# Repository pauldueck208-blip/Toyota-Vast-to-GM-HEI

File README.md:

# Toyota-Vast-to-GM-HEI
Board and code that interfaces between a GM HEI 8 pin and a 22re to replace the factory igniter.

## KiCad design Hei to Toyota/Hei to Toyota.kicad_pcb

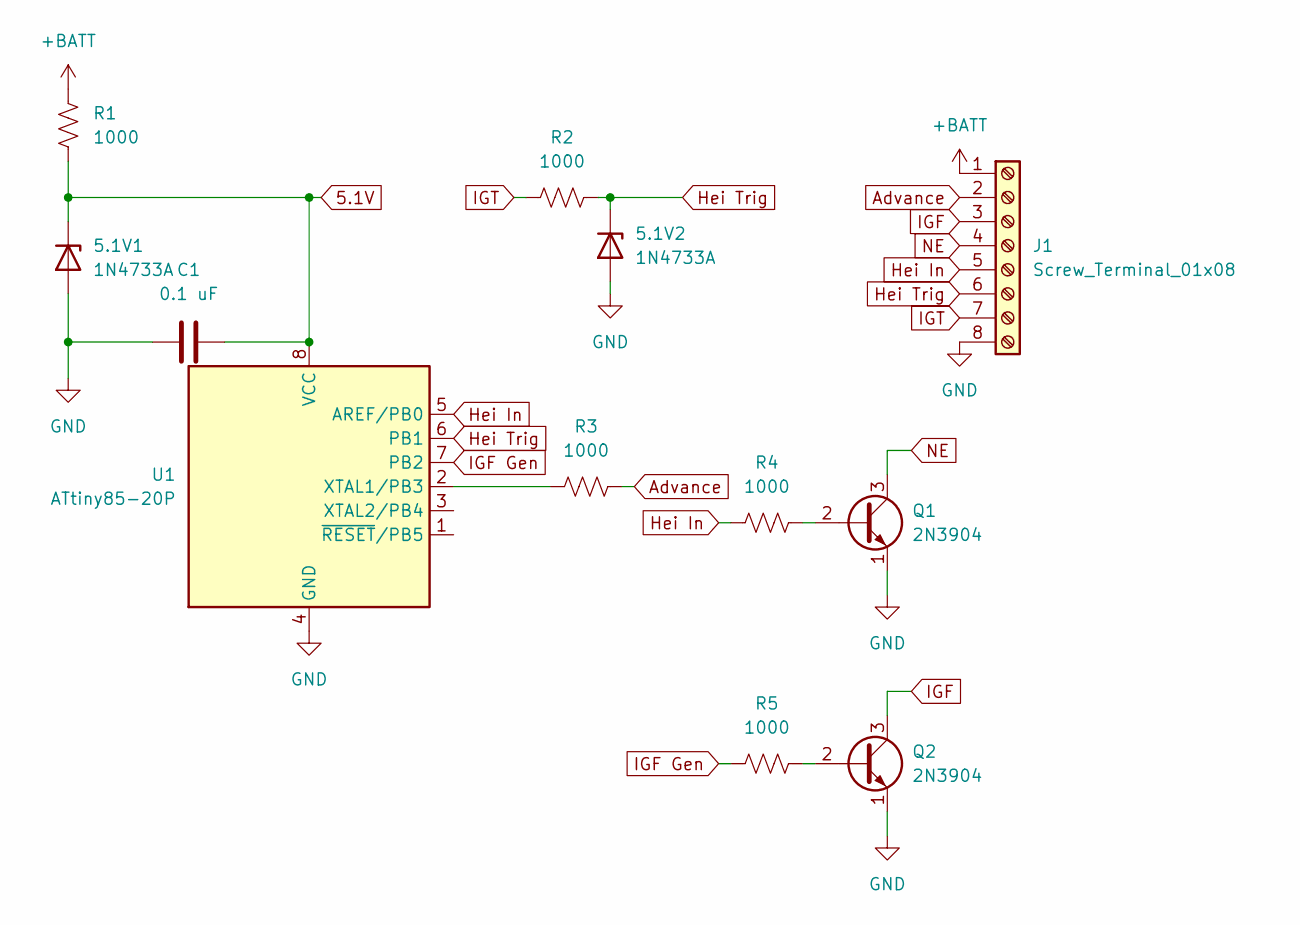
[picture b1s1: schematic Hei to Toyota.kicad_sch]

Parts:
5.1V1, 5.1V2: 1N4733A; D_DO-41_SOD81_P10.16mm_Horizontal
C1: 0.1 uF; C_Disc_D5.0mm_W2.5mm_P2.50mm
J1: Screw_Terminal_01x08; TerminalBlock_MaiXu_MX126-5.0-08P_1x08_P5.00mm
Q1, Q2: 2N3904; TO-92_Inline
R1, R2, R3, R4, R5: 1000; R_Axial_DIN0207_L6.3mm_D2.5mm_P10.16mm_Horizontal
U1: ATtiny85-20P; DIP-8_W7.62mm

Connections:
5.1V: 5.1V1.1 (K), C1.1, R1.1, U1.8 (VCC)
+BATT: J1.1, R1.2
Advance: J1.2, R3.2
GND: 5.1V1.2 (A), 5.1V2.2 (A), C1.2, J1.8, Q1.1 (E), Q2.1 (E), U1.4 (GND)
Hei In: J1.5, R4.1, U1.5 (AREF/PB0)
Hei Trig: 5.1V2.1 (K), J1.6, R2.2, U1.6 (PB1)
IGF: J1.3, Q2.3 (C)
IGF Gen: R5.1, U1.7 (PB2)
IGT: J1.7, R2.1
NE: J1.4, Q1.3 (C)
unnamed: Q1.2 (B), R4.2
unnamed: Q2.2 (B), R5.2
unnamed: R3.1, U1.2 (XTAL1/PB3)

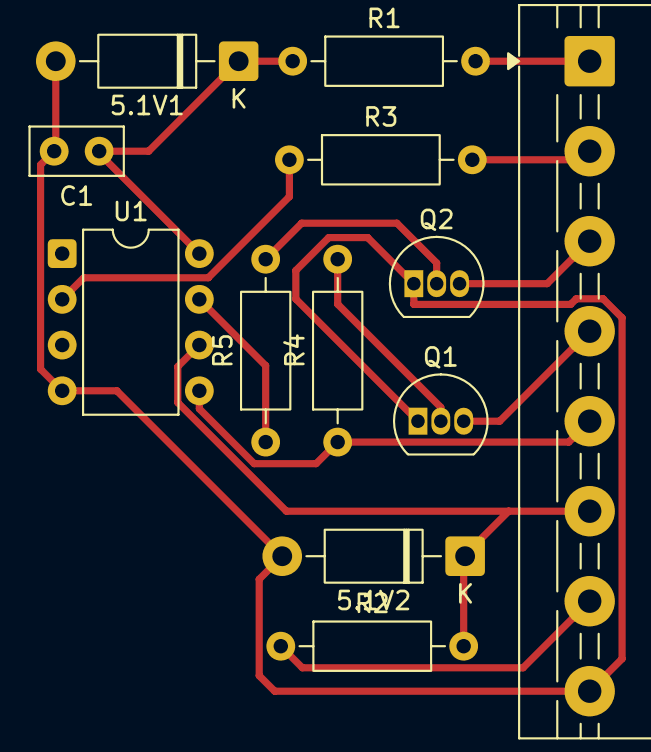
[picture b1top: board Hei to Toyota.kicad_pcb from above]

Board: 2 copper layers, 12 parts (0 on the bottom side), 13 nets.

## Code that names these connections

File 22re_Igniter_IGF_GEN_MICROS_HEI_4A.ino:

/*

      HEI to 22re code
      
The ecu for the 22re and Chevy's Hei igniter have send and recieve very similar signals. This code
determines what signal is reliable, IGT or NE, and sends 5v to the advance pin on the Hei. That will
switch it from using the signal it generates to make spark to the ecu signal. This code also generates
an IGF signal for the Toyota ecu to fire the injectors.

Created in 2026
Paul Dueck

*/
#include "MultiMap.h"
#include "PinChangeInterrupt.h"
const int IGF = 1;      // IGF output pin
const int NE = 3;       // NE input pin
const int IGT = 4;      // IGT input pin
const int HEITIME = 0;  // HEI timing ignore pin?

volatile bool IGF_trigger;        // Triggers IGF pulse
bool IGT_hap;                     // IGT State
byte IGT_times = 3;               // How many times IGT needs to come for Hei to switch to that signal.
volatile byte IGT_keep;           // Keeps track of how many times in succession IGT has been triggered.
volatile unsigned long IGT_last;  // Last time IGT was validated
const int IGT_drop = 300;         // Time before switch to NE
const int IGF_time = 1200;        // Duration of the IGF
unsigned long IFG_micros;         // To keep time


void setup() {
  pinMode(IGF, OUTPUT);
  pinMode(HEITIME, OUTPUT);
  pinMode(NE, INPUT_PULLUP);
  pinMode(IGT, INPUT_PULLUP);
  attachPCINT(digitalPinToPCINT(IGT), IGT_sense, FALLING);
  attachPCINT(digitalPinToPCINT(NE), NE_sense, FALLING);
  delay(20);  // Let the Arduino settle before work
}

void loop() {
  // IGF generation
  if (IGF_trigger == 1) {  //If the ISRs have been triggered, set output to high and reset the LOW timer
    digitalWrite(IGF, LOW);
    IFG_micros = micros();
    IGF_trigger = 0;
  }
  if (micros() - IFG_micros >= IGF_time) {  //If LOW timer has been reset, wait for set time then go LOW
    digitalWrite(IGF, HIGH);
  }

  // Hei IGT input switching
  if (IGT_keep >= IGT_times) {
    digitalWrite(HEITIME, HIGH);
  } else {
    digitalWrite(HEITIME, LOW);
  }

  if (millis() >= IGT_last + IGT_drop) {
    IGT_keep = 0;
    IGT_hap = 0;
  }
}

void IGT_sense() {  //IGT isr
  IGT_keep = IGT_keep + 1;
  IGT_calculate(IGT_keep, IGT_last, IGT_hap);
  if (IGT_hap = 1) {
    IGF_trigger = 1;
  }
}

void NE_sense() {  //NE isr
  if (IGT_hap = 1) {
    return;
  } else {
    IGF_trigger = 1;
  }
}

void IGT_calculate(int num, unsigned long lasttime, bool reliable) {
  if (num >= 3) {
    lasttime = millis;
    num = 0;
    reliable = 1;
  }
}
